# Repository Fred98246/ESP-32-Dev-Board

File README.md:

# Custom ESP32-S3-MINI-1 Development Board

## Overview
This repository contains the hardware design files for a custom ESP32-S3 4 layer development board. Built around the **ESP32-S3-MINI-1** module, this board is designed for flexible IoT development. 

The schematic and PCB layout were designed using **KiCad V6 E.D.A**.

**Schematic:**

**PCB:**

**Layers:**

**3D View:**

## Hardware Features
This development board includes:
* **Microcontroller:** ESP32-S3-MINI-1 (Wi-Fi & Bluetooth LE).
* **USB Interface:** USB Type-C receptacle with dedicated ESD protection (D3V3XA4B10LP).
* **Power Management:** 5V to 3.3V LDO regulator (TLV75801PDBV) with a dedicated power indicator LED.
* **Onboard Sensors & Outputs:**
  * **ENS210** Temperature and Humidity Sensor (connected via I2C).
  * **WS2812B** Addressable RGB LED for visual status feedback.
* **User Controls:** Physical `BOOT` and `RESET` tactile switches for easy flashing and debugging.
* **Expansion:** Two 22-pin headers breaking out GPIOs, I2C, UART, USB data lines, and power rails for easy breadboarding.

## Acknowledgements & Design Methodology
The design of this custom board was verified and optimized following the hardware design tutorials by **John Teel** at [Predictable Designs](https://predictabledesigns.com/). 

## Related Documents & Resources
For detailed specifications on the core components and reference designs, please consult the following official Espressif documentation:

* [ESP32-S3 Datasheet (PDF)](#)
* [ESP32-S3-MINI-1 & ESP32-S3-MINI-1U Datasheet (PDF)](#)
* [ESP32-S3-DevKitM-1 Schematic (PDF)](#)
* [ESP32-S3-DevKitM-1 PCB layout (PDF)](#)
* [ESP32-S3-DevKitM-1 Dimensions (PDF)](#)
* [ESP32-S3-DevKitM-1 Dimensions source file (DXF)](#) 

## Repository Structure
* `/Hardware` - KiCad project files (`.pro`, `.sch`, `.kicad_pcb`).
* `/Docs` - Exported schematics, BOM, and Gerber files for manufacturing.
* `/Firmware` - Example code for testing the WS2812B LED and ENS210 sensor.

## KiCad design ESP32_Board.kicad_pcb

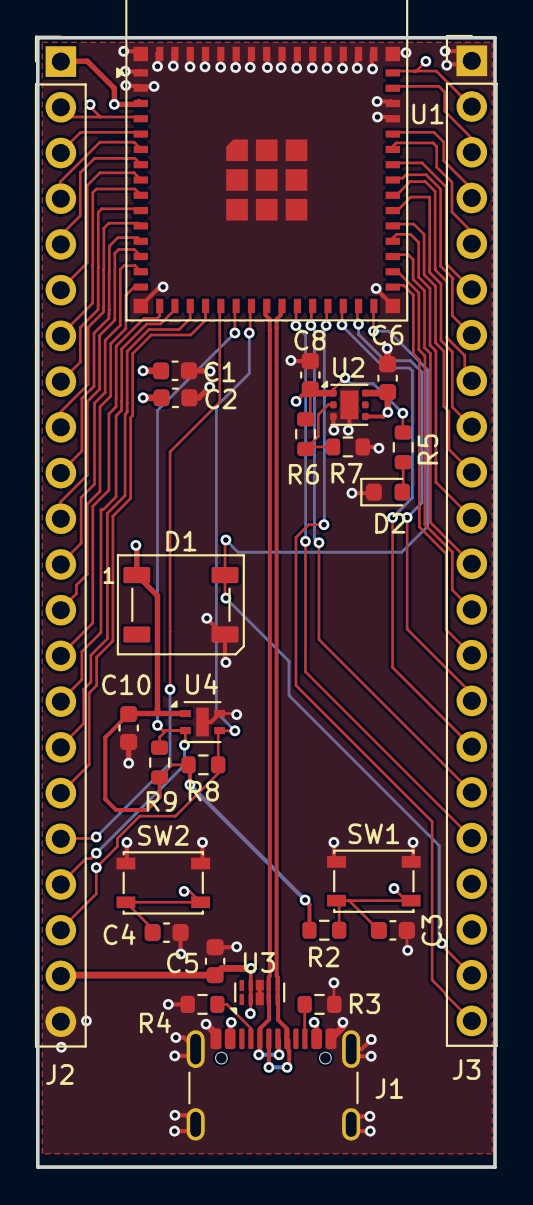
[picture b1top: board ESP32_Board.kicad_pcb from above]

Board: 4 copper layers, 25.4 x 62.7 mm, 27 parts (0 on the bottom side), 47 nets.

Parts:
C1, C5, C6, C8: 10u; C_0603_1608Metric
C2, C3, C4: 0.1u; C_0603_1608Metric
C10: 0.1U; C_0603_1608Metric
D1: WS2812B; LED_WS2812B_PLCC4_5.0x5.0mm_P3.2mm
D2: RED; LED_0603_1608Metric
J1: USB_C_Receptacle_USB2.0_16P; USB_C_Receptacle_GCT_USB4105-xx-A_16P_TopMnt_Horizontal
J2, J3: Conn_01x22_Pin; PinHeader_1x22_P2.54mm_Vertical
R2, R8, R9: 10K; R_0603_1608Metric
R3, R4, R5: 5.1K; R_0603_1608Metric
R6: 1M; R_0603_1608Metric
R7: 200k; R_0603_1608Metric
SW1: RESET; SW_SPST_PTS810
SW2: BOOT; SW_SPST_PTS810
U1: ESP32-S3-MINI-1; ESP32-S2-MINI-1
U2: TLV75801PDRV; WSON-6-1EP_2x2mm_P0.65mm_EP1x1.6mm
U3: D3V3XA4B10LP; Diodes_UDFN-10_1.0x2.5mm_P0.5mm
U4: ENS210; AMS_QFN-4-1EP_2x2mm_P0.95mm_EP0.7x1.6mm

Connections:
+3.3V: C1.1, C2.1, C8.1, C10.1, D1.1 (VDD), J2.1, R2.1, R5.1, R6.1, R8.1, R9.1, U1.3 (3V3), U2.1 (OUT), U4.1 (VDD)
+5V: C5.2, C6.1, J1.A4 (VBUS), J1.A9 (VBUS), J1.B4 (VBUS), J1.B9 (VBUS), J2.21, U2.4 (EN), U2.6 (IN), U3.2, U3.9 (NC)
/BOOT: C4.2, J2.2, SW2.2, U1.4 (IO0)
/EN: C3.2, J3.2, R2.2, SW1.2, U1.45 (EN)
/GPIO1: J2.3, U1.5 (IO1)
/GPIO2: J2.4, U1.6 (IO2)
/GPIO3: J2.5, U1.7 (IO3)
/GPIO4: J2.6, U1.8 (IO4)
/GPIO5: J2.7, U1.9 (IO5)
/GPIO6: J2.8, U1.10 (IO6)
/GPIO7: J2.9, U1.11 (IO7)
/GPIO8: J2.10, U1.12 (IO8)
/GPIO9: J2.11, U1.13 (IO9)
/GPIO10: J2.12, U1.14 (IO10)
/GPIO11: J2.13, U1.15 (IO11)
/GPIO12: J2.14, U1.16 (IO12)
/GPIO13: J2.15, U1.17 (IO13)
/GPIO14: J2.16, U1.18 (IO14)
/GPIO15: J2.17, U1.19 (IO15)
/GPIO16: J2.18, U1.20 (IO16)
/GPIO21: J3.18, U1.25 (IO21)
/GPIO26: J3.17, U1.26 (IO26)
/GPIO33: J3.16, U1.28 (IO33)
/GPIO34: J3.15, U1.29 (IO34)
/GPIO35: J3.14, U1.31 (IO35)
/GPIO36: J3.13, U1.32 (IO36)
/GPIO37: J3.12, U1.33 (IO37)
/GPIO38: J3.11, U1.34 (IO38)
/GPIO39: J3.10, U1.35 (IO39)
/GPIO40: J3.9, U1.36 (IO40)
/GPIO41: J3.8, U1.37 (IO41)
/GPIO42: J3.7, U1.38 (IO42)
/GPIO45: J3.4, U1.41 (IO45)
/GPIO46: J3.3, U1.44 (IO46)
/GPIO47: J3.22, U1.27 (IO47)
/GPIO48: D1.4 (DIN), J3.21, U1.30 (IO48)
/I2C_SCL: J2.19, R9.2, U1.21 (IO17), U4.2 (SCL)
/I2C_SDA: J2.20, R8.2, U1.22 (IO18), U4.3 (SDA)
/LED_POWER: D2.2 (A), R5.2
/RXD: J3.5, U1.40 (RXD0)
/TXD: J3.6, U1.39 (TXD0)
/USB_N: J1.A7 (D-), J1.B7 (D-), U1.23 (USB_D-), U3.4, U3.7 (NC)
/USB_P: J1.A6 (D+), J1.B6 (D+), U1.24 (USB_D+), U3.5, U3.6 (NC)
GND: C1.2, C2.2, C3.1, C4.1, C5.1, C6.2, C8.2, C10.2, D1.3 (VSS), D2.1 (K), J1.A1 (GND), J1.A12 (GND), J1.B1 (GND), J1.B12 (GND), J1.S1 (SHIELD), J2.22, J3.1, R3.2, R4.2, R7.2, SW1.1, SW2.1, U1.1 (GND), U1.2 (GND), U1.42 (GND), U1.43 (GND), U1.46 (GND), U1.47 (GND), U1.48 (GND), U1.49 (GND), U1.50 (GND), U1.51 (GND), U1.52 (GND), U1.53 (GND), U1.54 (GND), U1.55 (GND), U1.56 (GND), U1.57 (GND), U1.58 (GND), U1.59 (GND), U1.60 (GND), U1.61 (GND), U1.62 (GND), U1.63 (GND), U1.64 (GND), U1.65 (GND), U2.3 (GND), U2.7 (GND), U3.3 (VSS), U3.8 (VSS), U4.4 (GND), U4.5 (GND)
unnamed: J1.A5 (CC1), R4.1
unnamed: J1.B5 (CC2), R3.1
unnamed: R6.2, R7.1, U2.2 (FB)

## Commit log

2026-06-13 Enhance README with detailed project information
    Expanded the README to include an overview, hardware features, acknowledgements, related documents, repository structure, and author information.
2026-06-13 Create LICENSE
